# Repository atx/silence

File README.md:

# silence
A current controlled LED strip driver.

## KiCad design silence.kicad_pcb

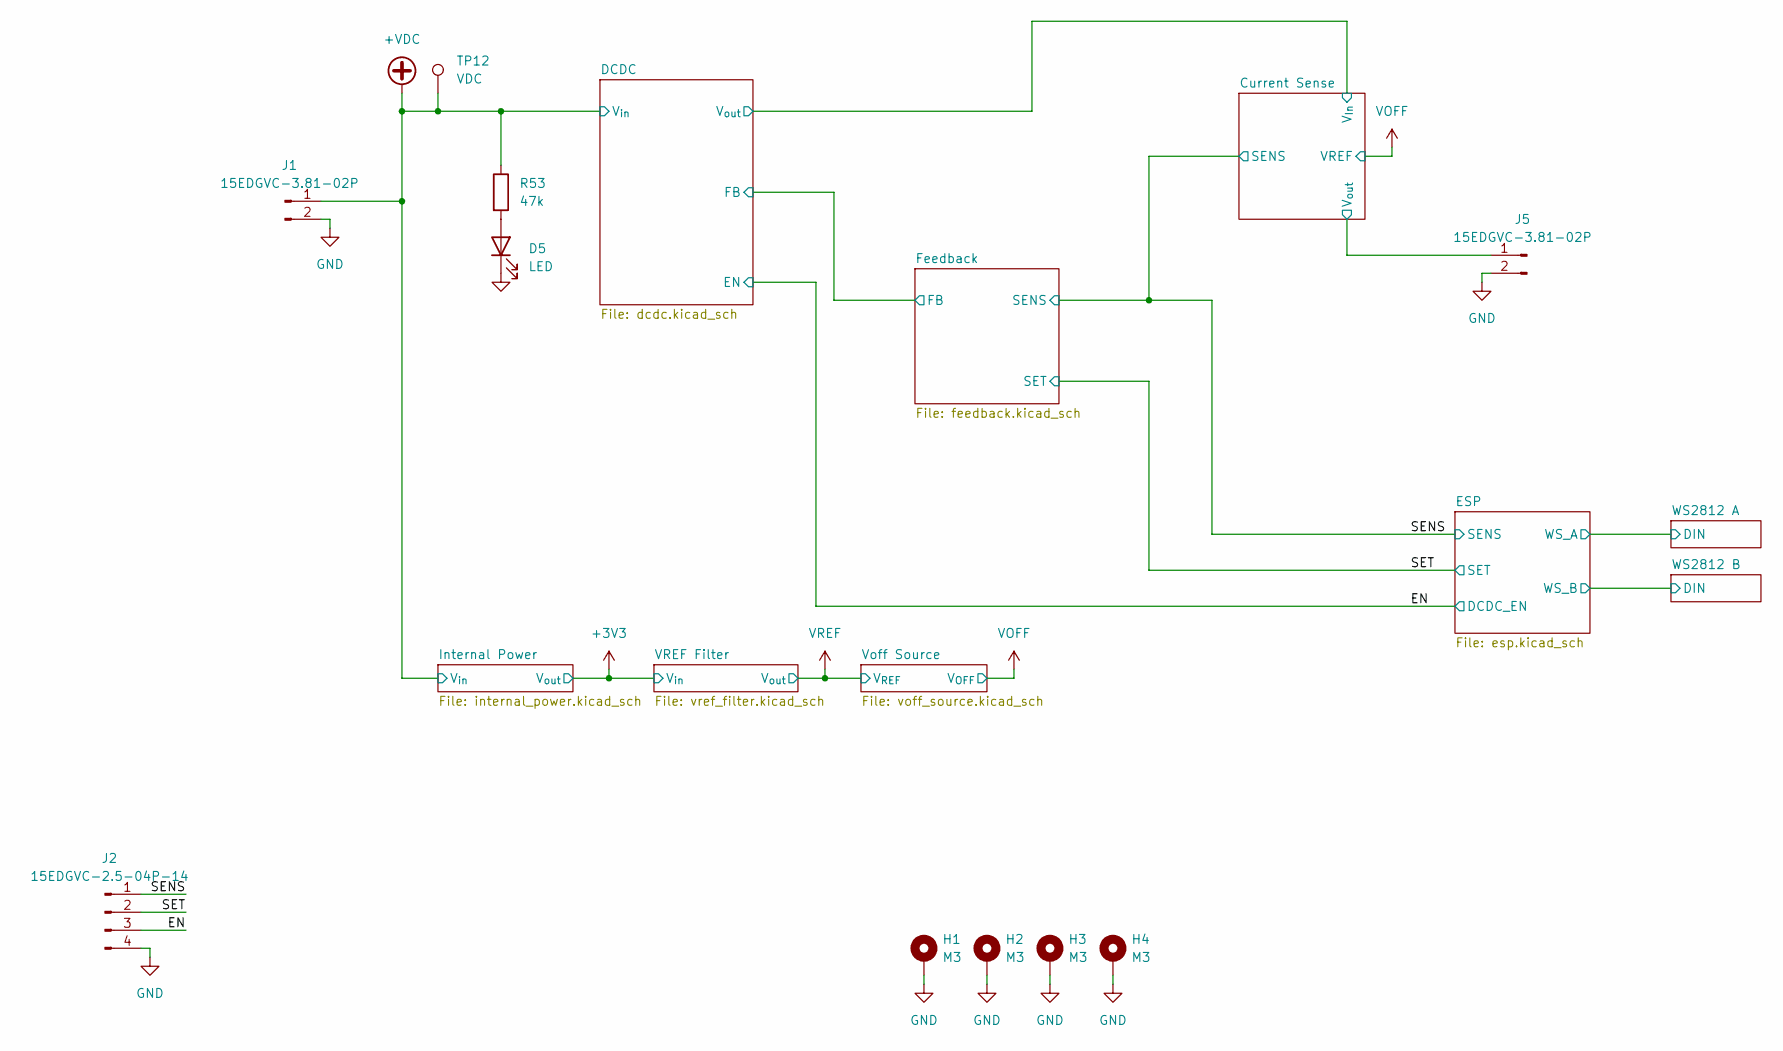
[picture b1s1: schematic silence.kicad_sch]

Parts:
D5: LED; LED_0603_1608Metric; LCSC C2290
H1, H2, H3, H4: M3; MountingHole_3.2mm_M3_Pad_Via_solid
J1, J5: 15EDGVC-3.81-02P; PhoenixContact_MCV_1,5_2-GF-3.81_1x02_P3.81mm_Vertical_Thre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
J2: 15EDGVC-2.5-04P-14
R53: 47k; R_0603_1608Metric; LCSC C25819
TP12: VDC; TestPoint_THTPad_D2.0mm_Drill1.0mm

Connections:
+VDC: J1.1, R53.1, TP12.1; also elsewhere on the board
/Current Sense/V_{out}: J5.1; also elsewhere on the board
/EN: J2.3; also elsewhere on the board
/SENS: J2.1; also elsewhere on the board
/SET: J2.2; also elsewhere on the board
GND: D5.1 (K), H1.1, H2.1, H3.1, H4.1, J1.2, J2.4, J5.2; also elsewhere on the board
unnamed: D5.2 (A), R53.2

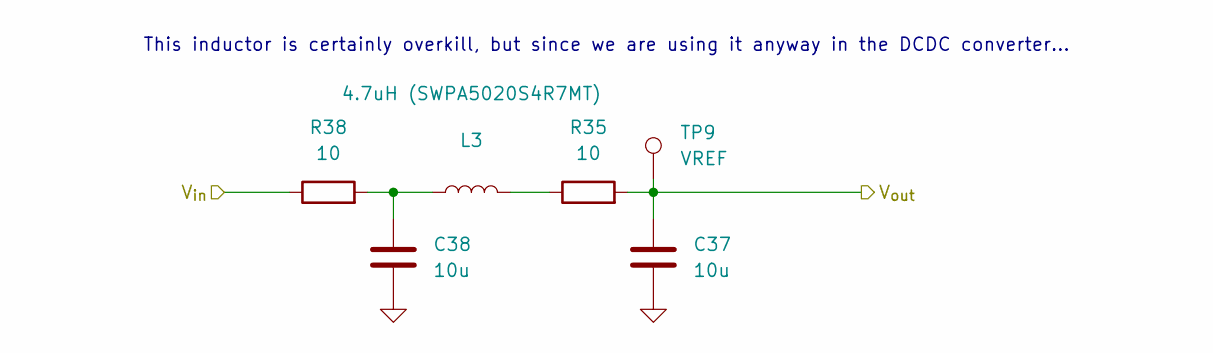
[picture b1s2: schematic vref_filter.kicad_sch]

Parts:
C37, C38: 10u; C_1206_3216Metric; LCSC C13585
L3: 4.7uH (SWPA5020S4R7MT); L_Sunlord_SWPA5020S; LCSC C43183
R35, R38: 10; R_0603_1608Metric; LCSC C22859
TP9: VREF; TestPoint_THTPad_D2.0mm_Drill1.0mm

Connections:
+3V3: R38.1; also elsewhere on the board
GND: C37.2, C38.2; also elsewhere on the board
unnamed: C38.1, L3.1, R38.2
unnamed: L3.2, R35.1
VREF: C37.1, R35.2, TP9.1; also elsewhere on the board

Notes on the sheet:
This inductor is certainly overkill, but since we are using it anyway in the DCDC converter...

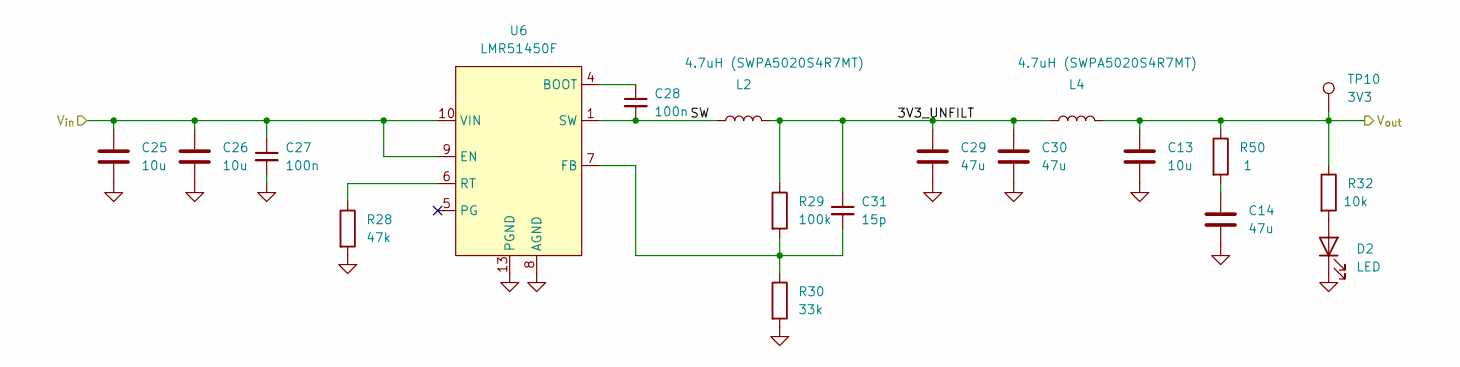
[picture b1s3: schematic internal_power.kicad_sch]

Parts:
C13, C25, C26: 10u; C_1206_3216Metric; LCSC C13585
C14, C29, C30: 47u; C_1206_3216Metric; LCSC C96123
C27, C28: 100n; C_0603_1608Metric; LCSC C14663
C31: 15p; C_0603_1608Metric; LCSC C1644
D2: LED; LED_0603_1608Metric; LCSC C2290
L2, L4: 4.7uH (SWPA5020S4R7MT); L_Sunlord_SWPA5020S; LCSC C43183
R28: 47k; R_0603_1608Metric; LCSC C25819
R29: 100k; R_0603_1608Metric; LCSC C25803
R30: 33k; R_0603_1608Metric; LCSC C4216
R32: 10k; R_0603_1608Metric; LCSC C25804
R50: 1; R_0603_1608Metric; LCSC C22936
TP10: 3V3; TestPoint_THTPad_D2.0mm_Drill1.0mm
U6: LMR51450F; WSON-12-1EP_3x3mm_P0.5mm_EP1.5x2.5mm_ThermalVias; LCSC C5782413

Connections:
+3V3: C13.1, L4.2, R32.1, R50.1, TP10.1; also elsewhere on the board
+VDC: C25.1, C26.1, C27.1, U6.9 (EN), U6.10 (VIN), U6.11 (VIN), U6.12 (VIN); also elsewhere on the board
/Internal Power/3V3_UNFILT: C29.1, C30.1, C31.1, L2.2, L4.1, R29.1
/Internal Power/SW: C28.2, L2.1, U6.1 (SW), U6.2 (SW), U6.3 (SW)
GND: C13.2, C14.2, C25.2, C26.2, C27.2, C29.2, C30.2, D2.1 (K), R28.2, R30.2, U6.8 (AGND), U6.13 (PGND); also elsewhere on the board
unnamed: C14.1, R50.2
unnamed: D2.2 (A), R32.2
unnamed: C28.1, U6.4 (BOOT)
unnamed: C31.2, R29.2, R30.1, U6.7 (FB)
unnamed: R28.1, U6.6 (RT)

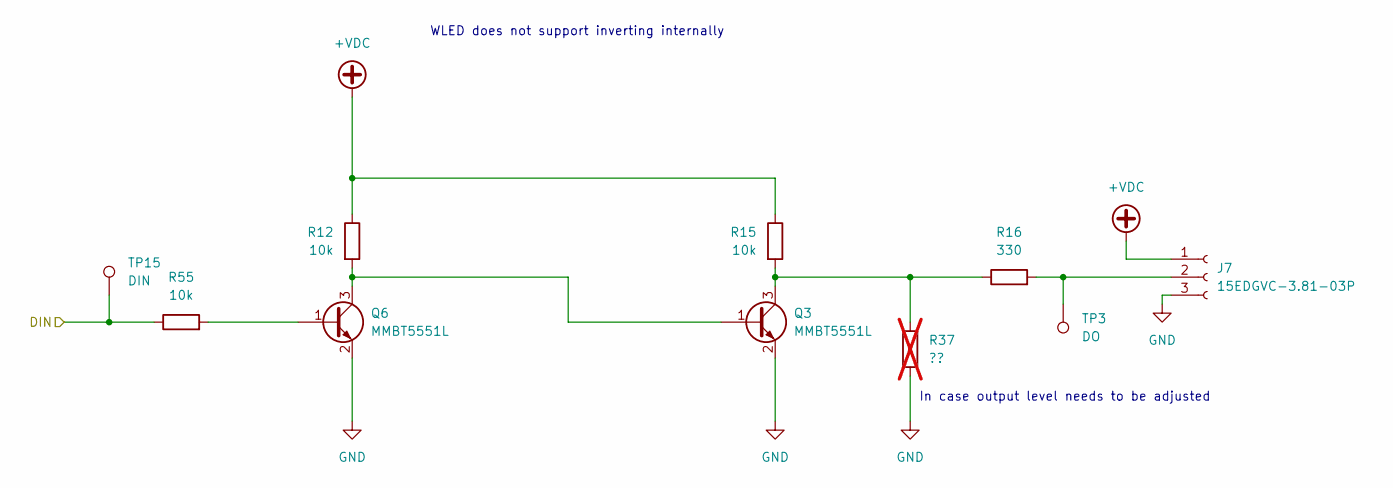
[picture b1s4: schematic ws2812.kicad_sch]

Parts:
J7: 15EDGVC-3.81-03P; PhoenixContact_MCV_1,5_3-G-3.81_1x03_P3.81mm_Vertical
Q3, Q6: MMBT5551L; SOT-23; LCSC C2145
R12, R15, R55: 10k; R_0603_1608Metric; LCSC C25804
R16: 330; R_0603_1608Metric; LCSC C23138
R37: ??; R_0603_1608Metric; not fitted
TP3: DO; TestPoint_THTPad_D1.5mm_Drill0.7mm
TP15: DIN; TestPoint_THTPad_D1.5mm_Drill0.7mm

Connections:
+VDC: J7.1, R12.1, R15.1; also elsewhere on the board
/ESP/WS_A: R55.1, TP15.1; also elsewhere on the board
GND: J7.3, Q3.2 (E), Q6.2 (E), R37.2; also elsewhere on the board
unnamed: J7.2, R16.2, TP3.1
unnamed: Q3.1 (B), Q6.3 (C), R12.2
unnamed: Q3.3 (C), R15.2, R16.1, R37.1
unnamed: Q6.1 (B), R55.2

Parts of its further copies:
J4: 15EDGVC-3.81-03P; PhoenixContact_MCV_1,5_3-G-3.81_1x03_P3.81mm_Vertical
Q1, Q5: MMBT5551L; SOT-23; LCSC C2145
R18, R20, R54: 10k; R_0603_1608Metric; LCSC C25804
R21: 330; R_0603_1608Metric; LCSC C23138
R36: ??; R_0603_1608Metric; not fitted
TP1: DO; TestPoint_THTPad_D1.5mm_Drill0.7mm
TP2: DIN; TestPoint_THTPad_D1.5mm_Drill0.7mm

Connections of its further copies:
+VDC: J4.1, R18.1, R20.1; also elsewhere on the board
/ESP/WS_B: R54.1, TP2.1; also elsewhere on the board
GND: J4.3, Q1.2 (E), Q5.2 (E), R36.2; also elsewhere on the board
unnamed: J4.2, R21.2, TP1.1
unnamed: Q1.1 (B), Q5.3 (C), R18.2
unnamed: Q1.3 (C), R20.2, R21.1, R36.1
unnamed: Q5.1 (B), R54.2

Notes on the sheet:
WLED does not support inverting internally
In case output level needs to be adjusted

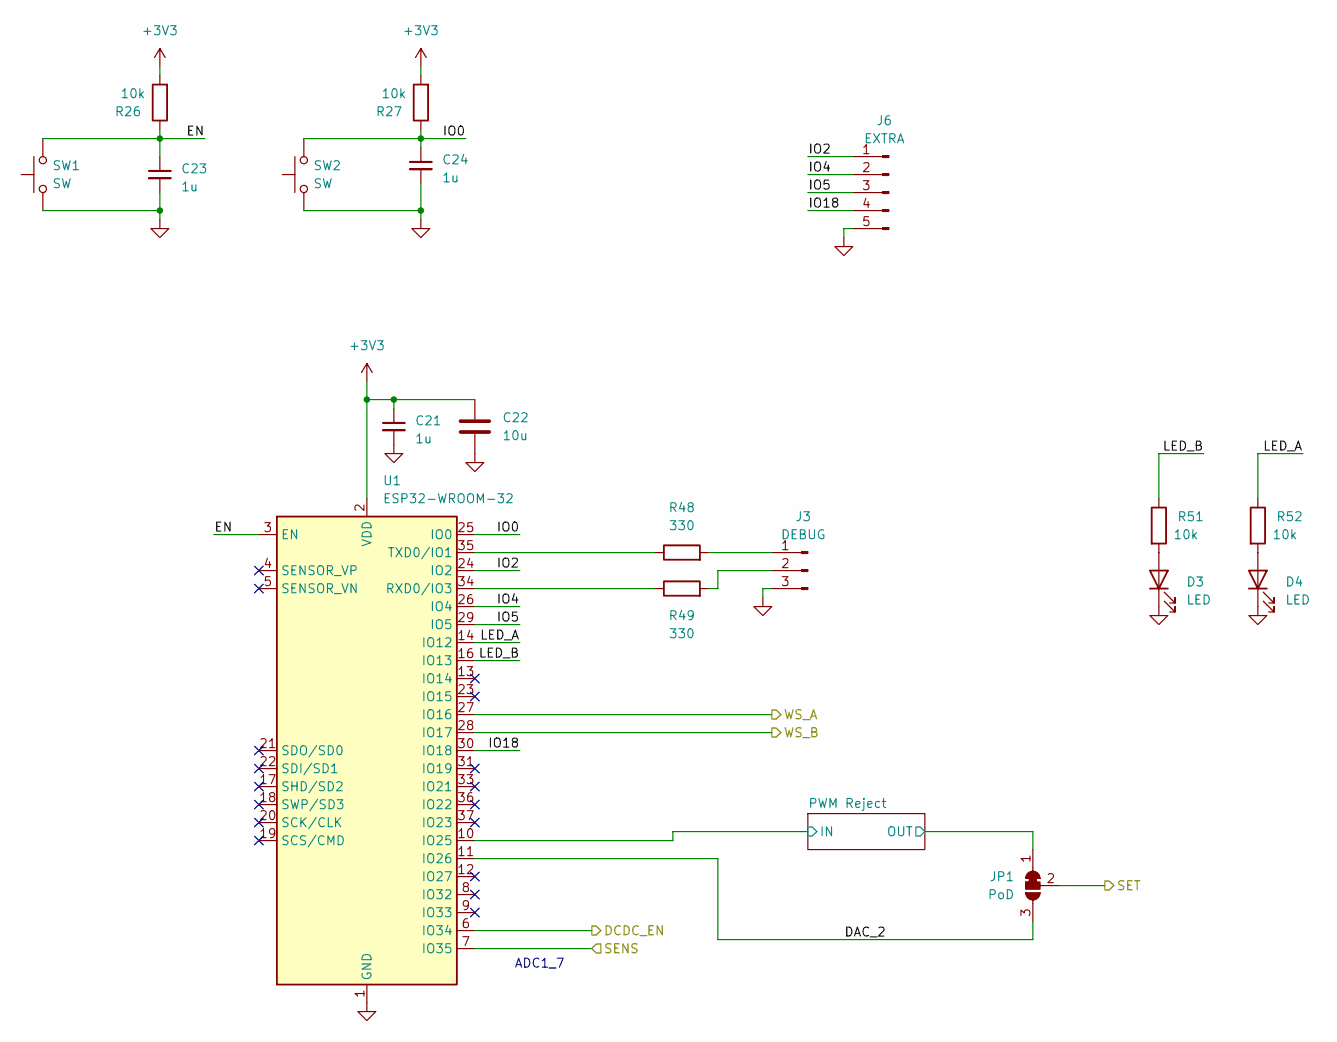
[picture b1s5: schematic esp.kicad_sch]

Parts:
C21, C23, C24: 1u; C_0603_1608Metric; LCSC C15849
C22: 10u; C_1206_3216Metric; LCSC C13585
D3, D4: LED; LED_0603_1608Metric; LCSC C2290
J3: DEBUG; PinHeader_1x03_P2.54mm_Vertical
J6: EXTRA; PinHeader_1x05_P2.54mm_Vertical
JP1: PoD; SolderJumper-3_P1.3mm_Bridged12_RoundedPad1.0x1.5mm
R26, R27, R51, R52: 10k; R_0603_1608Metric; LCSC C25804
R48, R49: 330; R_0603_1608Metric; LCSC C23138
SW1, SW2: SW; SW_PUSH_6mm_H4.3mm
U1: ESP32-WROOM-32

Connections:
+3V3: C21.1, C22.1, R26.2, R27.2, U1.2 (VDD); also elsewhere on the board
/EN: U1.6 (IO34); also elsewhere on the board
/ESP/DAC_2: JP1.3 (B), U1.11 (IO26)
/ESP/EN: C23.1, R26.1, SW1.2, U1.3 (EN)
/ESP/IO0: C24.1, R27.1, SW2.2, U1.25 (IO0)
/ESP/IO2: J6.1, U1.24 (IO2)
/ESP/IO4: J6.2, U1.26 (IO4)
/ESP/IO5: J6.3, U1.29 (IO5)
/ESP/IO18: J6.4, U1.30 (IO18)
/ESP/LED_A: R52.1, U1.14 (IO12)
/ESP/LED_B: R51.1, U1.16 (IO13)
/ESP/PWM Reject/IN: U1.10 (IO25); also elsewhere on the board
/ESP/PWM Reject/OUT: JP1.1 (A); also elsewhere on the board
/ESP/WS_A: U1.27 (IO16); also elsewhere on the board
/ESP/WS_B: U1.28 (IO17); also elsewhere on the board
/SENS: U1.7 (IO35); also elsewhere on the board
/SET: JP1.2 (C); also elsewhere on the board
GND: C21.2, C22.2, C23.2, C24.2, D3.1 (K), D4.1 (K), J3.3, J6.5, SW1.1, SW2.1, U1.1 (GND), U1.15 (GND), U1.38 (GND), U1.39 (GND); also elsewhere on the board
unnamed: D3.2 (A), R51.2
unnamed: D4.2 (A), R52.2
unnamed: J3.1, R48.2
unnamed: J3.2, R49.2
unnamed: R49.1, U1.34 (RXD0/IO3)
unnamed: R48.1, U1.35 (TXD0/IO1)

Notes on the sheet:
ADC1_7

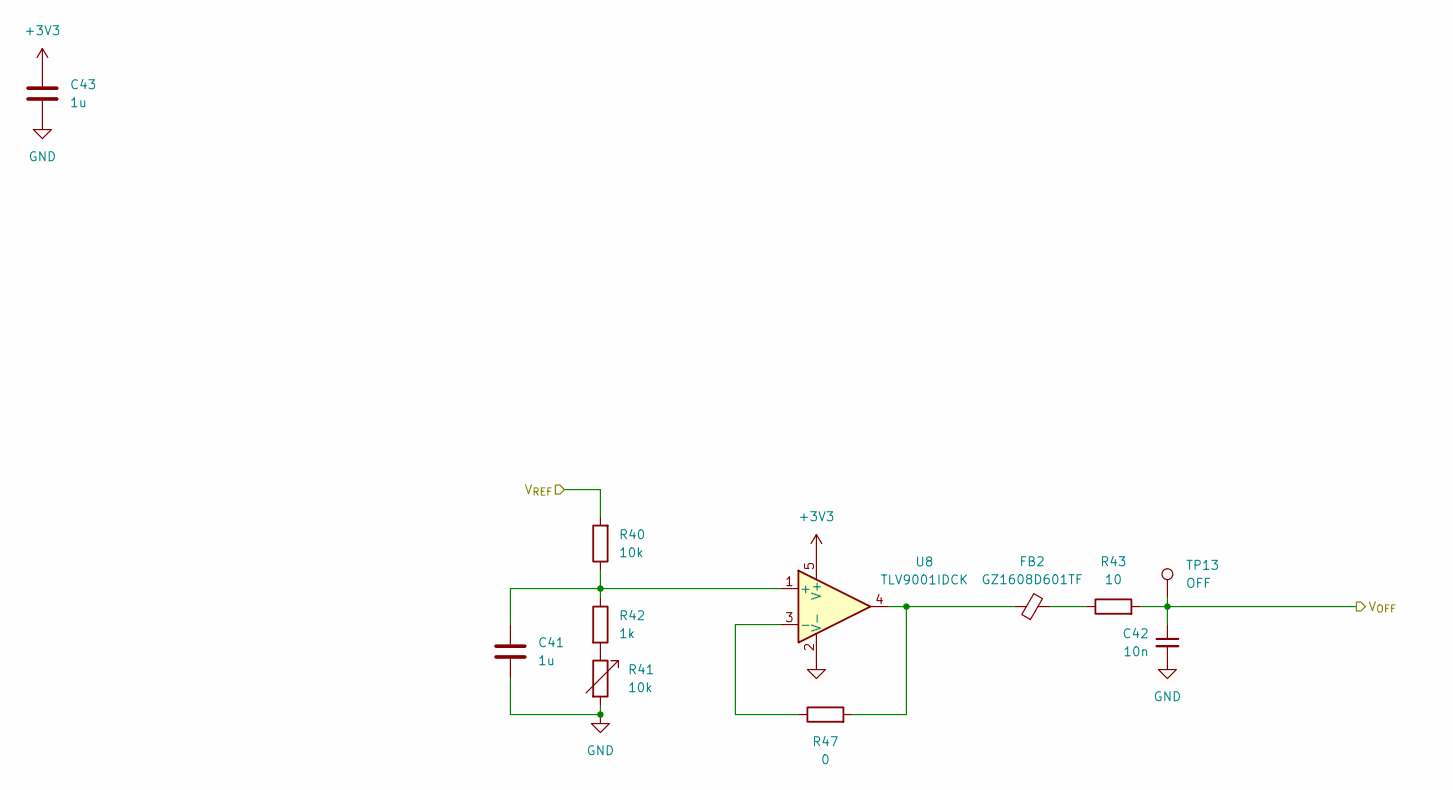
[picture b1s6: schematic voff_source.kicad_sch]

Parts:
C41, C43: 1u; C_0603_1608Metric; LCSC C15849
C42: 10n; C_0603_1608Metric; LCSC C57112
FB2: GZ1608D601TF; L_0603_1608Metric; LCSC C1002
R40: 10k; R_0603_1608Metric; LCSC C25804
R41: 10k; Potentiometer_Bourns_3296W_Vertical
R42: 1k; R_0603_1608Metric; LCSC C21190
R43: 10; R_0603_1608Metric; LCSC C22859
R47: 0; R_0603_1608Metric; LCSC C21189
TP13: OFF; TestPoint_THTPad_D2.0mm_Drill1.0mm
U8: TLV9001IDCK; SOT-353_SC-70-5; LCSC C398362

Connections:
+3V3: C43.1, U8.5 (V+); also elsewhere on the board
GND: C41.2, C42.2, C43.2, R41.2, U8.2 (V-); also elsewhere on the board
unnamed: FB2.1, R47.2, U8.4
unnamed: FB2.2, R43.1
unnamed: R41.1, R42.2
unnamed: C41.1, R40.1, R42.1, U8.1 (+)
unnamed: R47.1, U8.3 (-)
VOFF: C42.1, R43.2, TP13.1; also elsewhere on the board
VREF: R40.2; also elsewhere on the board

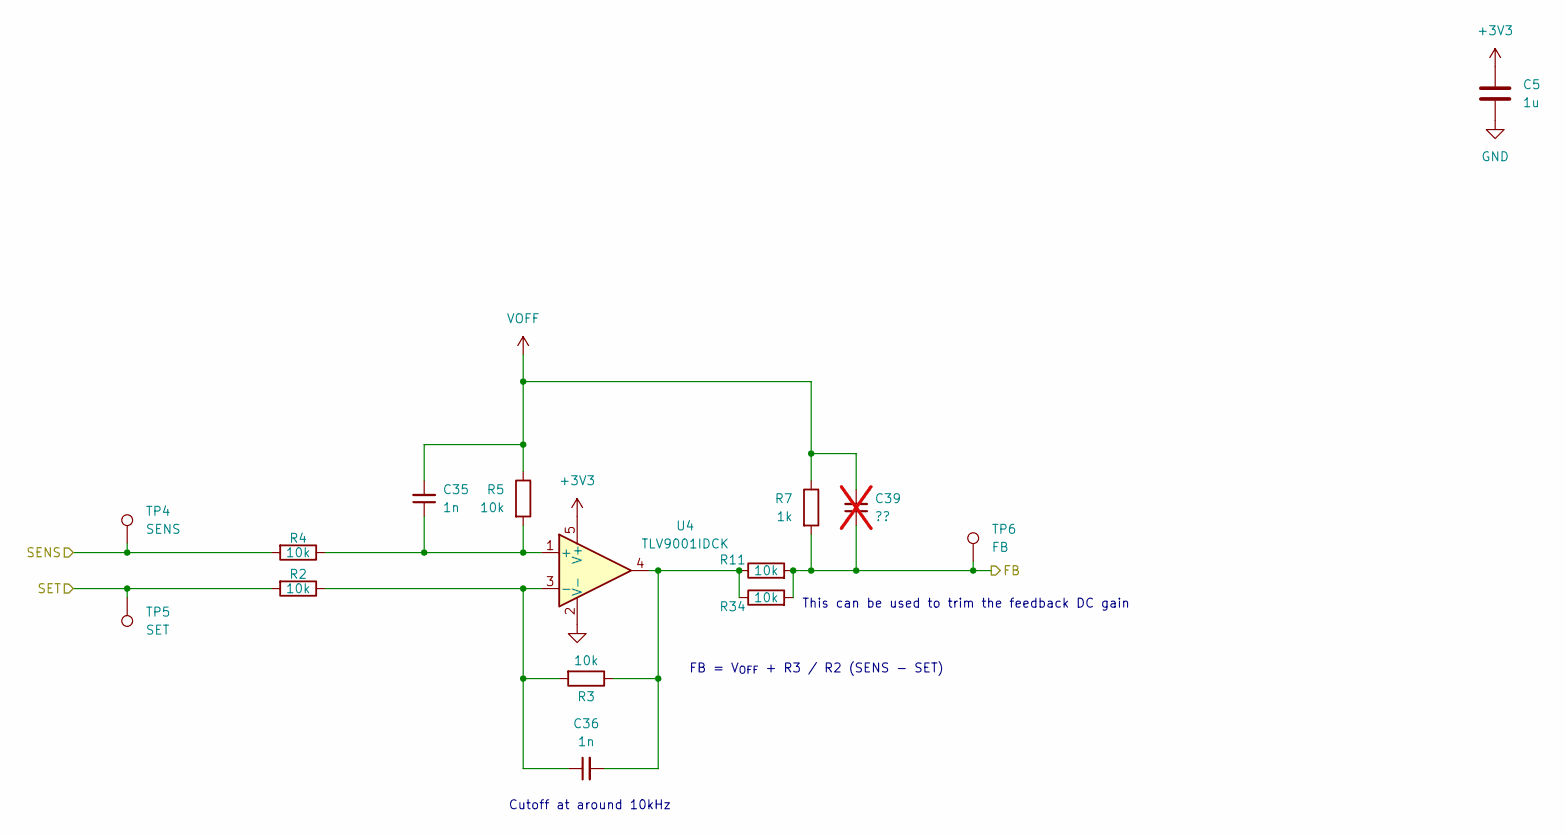
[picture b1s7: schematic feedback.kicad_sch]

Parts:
C5: 1u; C_0603_1608Metric; LCSC C15849
C35, C36: 1n; C_0603_1608Metric; LCSC C1588
C39: ??; C_0603_1608Metric; not fitted
R2, R3, R4, R5, R11, R34: 10k; R_0603_1608Metric; LCSC C25804
R7: 1k; R_0603_1608Metric; LCSC C21190
TP4: SENS; TestPoint_THTPad_D1.5mm_Drill0.7mm
TP5: SET; TestPoint_THTPad_D1.5mm_Drill0.7mm
TP6: FB; TestPoint_THTPad_D1.5mm_Drill0.7mm
U4: TLV9001IDCK; SOT-353_SC-70-5; LCSC C398362

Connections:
+3V3: C5.1, U4.5 (V+); also elsewhere on the board
/DCDC/FB: C39.1, R7.2, R11.2, R34.2, TP6.1; also elsewhere on the board
/SENS: R4.2, TP4.1; also elsewhere on the board
/SET: R2.2, TP5.1; also elsewhere on the board
GND: C5.2, U4.2 (V-); also elsewhere on the board
unnamed: C36.2, R3.1, R11.1, R34.1, U4.4
unnamed: C35.1, R4.1, R5.2, U4.1 (+)
unnamed: C36.1, R2.1, R3.2, U4.3 (-)
VOFF: C35.2, C39.2, R5.1, R7.1; also elsewhere on the board

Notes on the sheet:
FB = V_{OFF} + R3 / R2 (SENS - SET)
This can be used to trim the feedback DC gain
Cutoff at around 10kHz

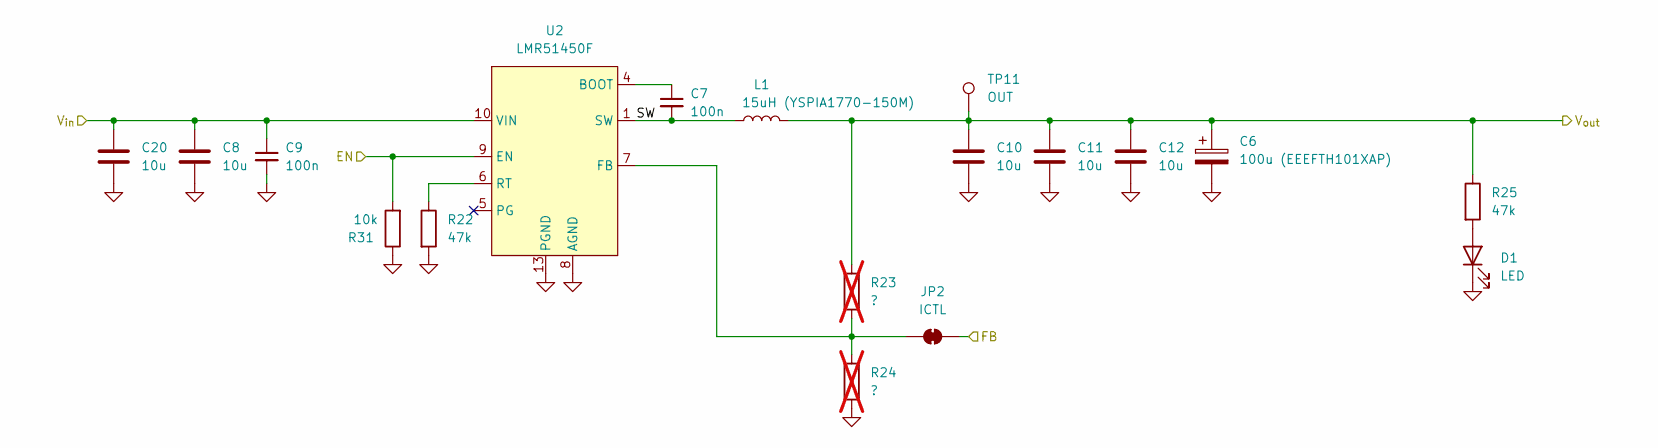
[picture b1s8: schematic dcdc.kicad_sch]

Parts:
C6: 100u (EEEFTH101XAP); CP_Elec_6.3x7.7
C7, C9: 100n; C_0603_1608Metric; LCSC C14663
C8, C10, C11, C12, C20: 10u; C_1206_3216Metric; LCSC C13585
D1: LED; LED_0603_1608Metric; LCSC C2290
JP2: ICTL; SolderJumper-2_P1.3mm_Bridged_RoundedPad1.0x1.5mm
L1: 15uH (YSPIA1770-150M); YSPIA1770; LCSC C2839931
R22, R25: 47k; R_0603_1608Metric; LCSC C25819
R23, R24: ?; R_0603_1608Metric; not fitted
R31: 10k; R_0603_1608Metric; LCSC C25804
TP11: OUT; TestPoint_THTPad_D2.0mm_Drill1.0mm
U2: LMR51450F; WSON-12-1EP_3x3mm_P0.5mm_EP1.5x2.5mm_ThermalVias; LCSC C5782413

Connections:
+VDC: C8.1, C9.1, C20.1, U2.10 (VIN), U2.11 (VIN), U2.12 (VIN); also elsewhere on the board
/Current Sense/V_{In}: C6.1, C10.1, C11.1, C12.1, L1.2, R23.1, R25.1, TP11.1; also elsewhere on the board
/DCDC/FB: JP2.2 (B); also elsewhere on the board
/DCDC/SW: C7.2, L1.1, U2.1 (SW), U2.2 (SW), U2.3 (SW)
/EN: R31.2, U2.9 (EN); also elsewhere on the board
GND: C6.2, C8.2, C9.2, C10.2, C11.2, C12.2, C20.2, D1.1 (K), R22.2, R24.2, R31.1, U2.8 (AGND), U2.13 (PGND); also elsewhere on the board
unnamed: D1.2 (A), R25.2
unnamed: JP2.1 (A), R23.2, R24.1, U2.7 (FB)
unnamed: C7.1, U2.4 (BOOT)
unnamed: R22.1, U2.6 (RT)

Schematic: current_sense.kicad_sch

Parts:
C32: 1n; C_0603_1608Metric; Manufacturer_Part_Number C1608JB2A102M080AA; LCSC C1588
C33, C34: 100n; C_0402_1005Metric; Manufacturer_Part_Number CC0603KRX7R9BB104; LCSC C307331
R33: 10mR 1206; R_1206_3216Metric; Manufacturer_Part_Number PA0805FRF470R005L; LCSC C105362
TP8: I_{OUT}; TestPoint_THTPad_D2.0mm_Drill1.0mm
U7: INA241A2IDDFR; SOT65P280X110-8N; Mouser Part Number 595-INA241A1IDDFR

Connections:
+3V3: C33.1, U7.6 (VCC); also elsewhere on the board
/Current Sense/V_{In}: R33.2, U7.8 (IN+); also elsewhere on the board
/Current Sense/V_{out}: C32.2, R33.1, U7.1 (IN-); also elsewhere on the board
/SENS: TP8.1, U7.5 (OUT); also elsewhere on the board
GND: C32.1, C33.2, C34.2, U7.2 (GND); also elsewhere on the board
VOFF: C34.1, U7.3 (REF2), U7.7 (REF1); also elsewhere on the board

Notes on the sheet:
20V/V VfsIN = 50mV Ifs = 5 A VfsOUT = +-1.0V -> 1A <=> 200 mV

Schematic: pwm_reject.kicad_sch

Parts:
C1, C4: 1u; C_0603_1608Metric; LCSC C15849
C2, C3: 10n; C_0603_1608Metric; LCSC C57112
R1: 10k; Potentiometer_Bourns_3296W_Vertical
R6: 100; R_0603_1608Metric; LCSC C25804
R8, R9, R10, R39, R44, R45: 10k; R_0603_1608Metric; LCSC C25804
R46: 100k; R_0603_1608Metric; not fitted
TP7: PWM; TestPoint_THTPad_D1.5mm_Drill0.7mm
TP14: F1; TestPoint_THTPad_D1.5mm_Drill0.7mm
U3, U5: TLV9001IDCK; SOT-353_SC-70-5; LCSC C398362

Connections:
+3V3: C1.1, C4.1, U3.5 (V+), U5.5 (V+); also elsewhere on the board
/ESP/PWM Reject/IN: R9.1, TP7.1; also elsewhere on the board
/ESP/PWM Reject/OUT: R8.2, U3.4; also elsewhere on the board
GND: C1.2, C2.2, C4.2, R1.2, R45.1, R46.1, U3.2 (V-), U5.2 (V-); also elsewhere on the board
unnamed: C3.1, R6.2, R9.2, R10.1
unnamed: R1.1, R6.1
unnamed: R39.2, R44.2, R46.2, U3.1 (+)
unnamed: R8.1, R45.2, U3.3 (-)
unnamed: C2.1, R10.2, U5.1 (+)
unnamed: C3.2, R39.1, TP14.1, U5.3 (-), U5.4
VOFF: R44.1; also elsewhere on the board

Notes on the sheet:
This may be needed to nullify offset somewhere
0V - 1V
0.5V - 1.0V
Pot sets maximum current
1.0V - 2.0V

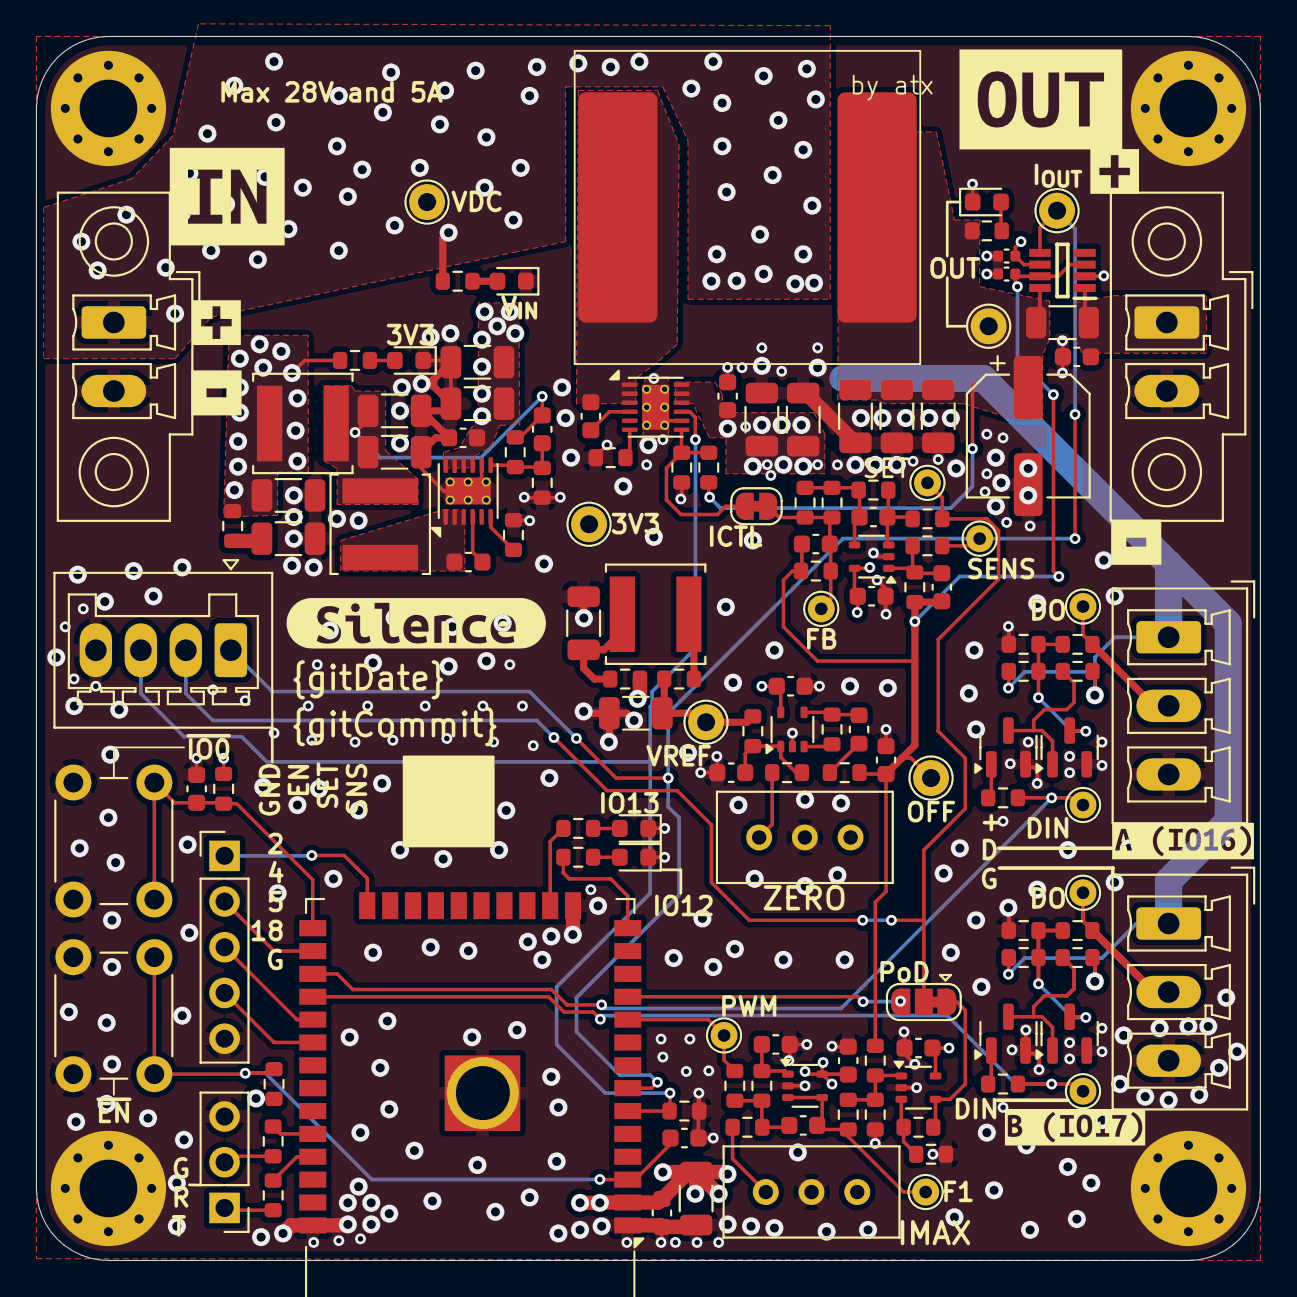
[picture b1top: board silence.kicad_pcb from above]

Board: 4 copper layers, 68.0 x 68.0 mm, 149 parts (0 on the bottom side), 67 nets.

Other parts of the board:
kibuzzard-676F24DA: G***; kibuzzard-676F24DA
kibuzzard-676F24FA: G***; kibuzzard-676F24FA
kibuzzard-676F26EA: G***; kibuzzard-676F26EA
kibuzzard-676F239E, kibuzzard-676F239E#2: G***; kibuzzard-676F239E
kibuzzard-676F243D: G***; kibuzzard-676F243D
kibuzzard-676F2404, kibuzzard-676F2404#2: G***; kibuzzard-676F2404
kibuzzard-676F2425: G***; kibuzzard-676F2425

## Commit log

2024-12-22 Initial schematic commit
2024-12-23 Start layout
2024-12-23 Minor updates
2024-12-27 Routing almost finished
2025-01-01 Minor edits
2025-01-04 Manufacturing update + inductor fix
2025-02-22 case: Initial model of the bottom part
